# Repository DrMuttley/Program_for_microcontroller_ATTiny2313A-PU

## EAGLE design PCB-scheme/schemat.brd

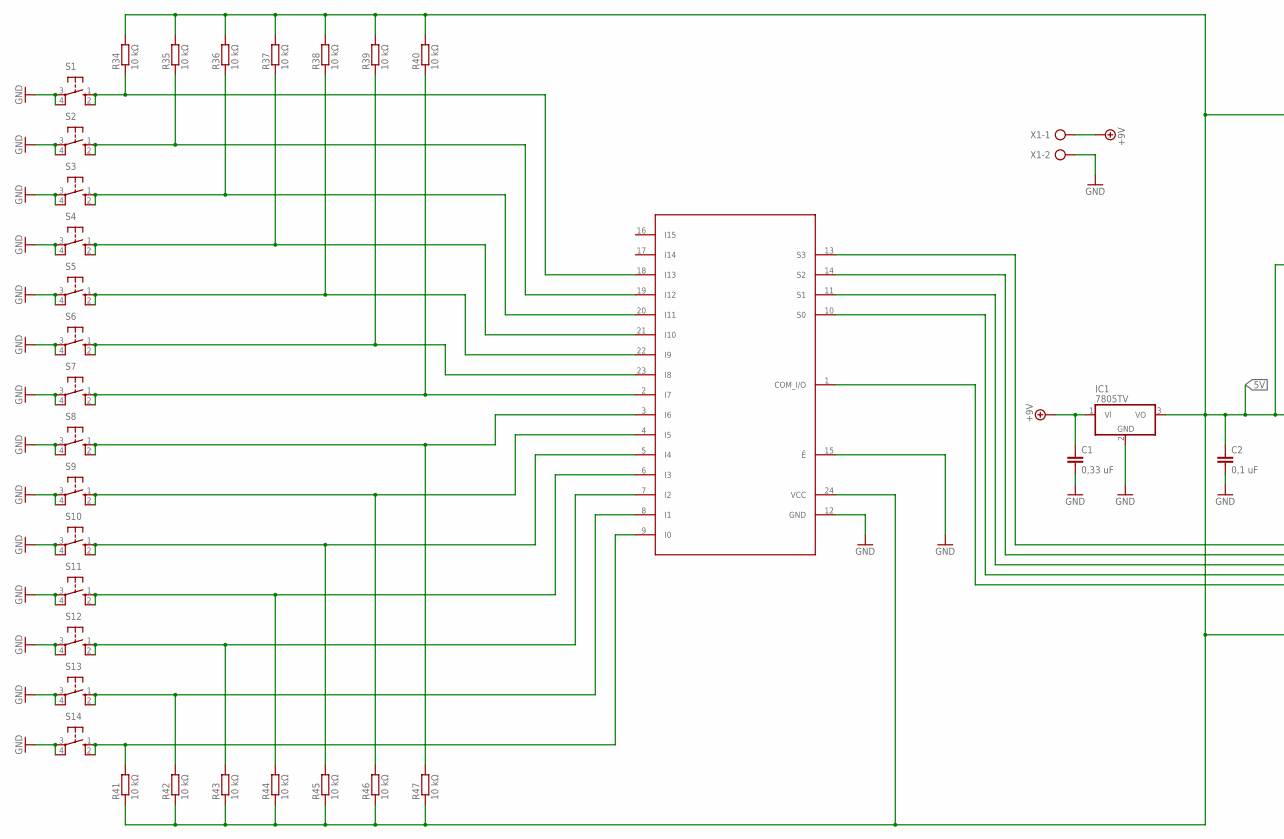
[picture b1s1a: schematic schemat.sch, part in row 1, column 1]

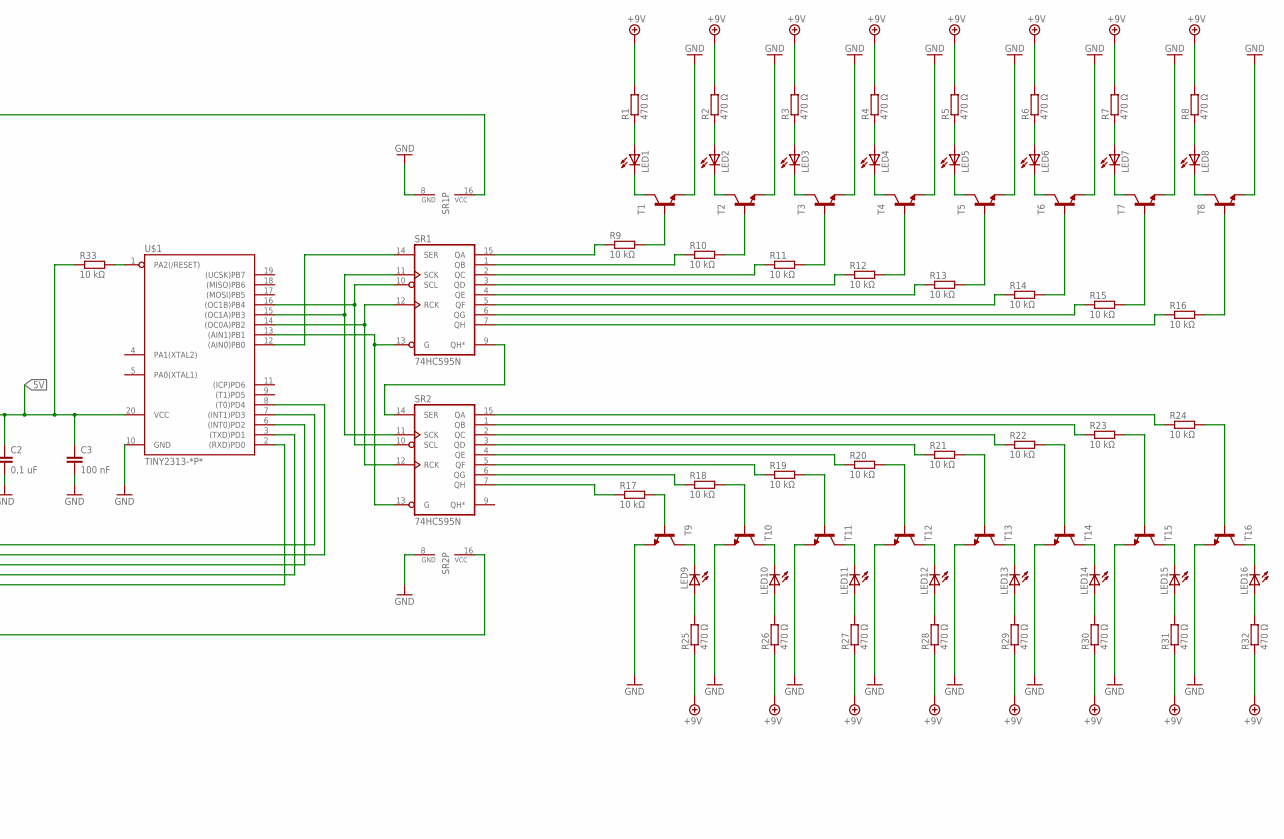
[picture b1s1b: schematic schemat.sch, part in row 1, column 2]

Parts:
C1: 0,33 uF; C025-024X044
C2: 0,1 uF; C025-024X044
C3: 100 nF; C025-024X044
IC1: 7805TV; TO220V
LED1, LED2, LED3, LED4, LED5, LED6, LED7, LED8, LED9, LED10, LED11, LED12, LED13, LED14, LED15, LED16: LED5MM
R1, R2, R3, R4, R5, R6, R7, R8, R25, R26, R27, R28, R29, R30, R31, R32: 470 Ω; 0207/10
R9, R10, R11, R12, R13, R14, R15, R16, R17, R18, R19, R20, R21, R22, R23, R24, R33, R34, R35, R36, R37, R38, R39, R40, R41, R42, R43, R44, R45, R46, R47: 10 kΩ; 0207/10
S1, S2, S3, S4, S5, S6, S7, S8, S9, S10, S11, S12, S13, S14: 40-XX; B3F-40XX
SR1, SR2: 74HC595N; DIL16
T1, T2, T3, T4, T5, T6, T7, T8, T9, T10, T11, T12, T13, T14, T15, T16: -NPN-TO92; TO92
U$1: TINY2313-*P*; DIL20
U$2: CD74HC4067; DIL24-6
X1: AK500/2

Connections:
5V: C2.1, C3.1, IC1.3 (VO), R33.1, R34.2, R35.2, R36.2, R37.2, R38.2, R39.2, R40.2, R41.1, R42.1, R43.1, R44.1, R45.1, R46.1, R47.1, SR1.16 (VCC), SR2.16 (VCC), U$1.20 (VCC), U$2.24 (VCC)
+9V: C1.1, IC1.1 (VI), R1.2, R2.2, R3.2, R4.2, R5.2, R6.2, R7.2, R8.2, R25.1, R26.1, R27.1, R28.1, R29.1, R30.1, R31.1, R32.1, X1.1
GND: C1.2, C2.2, C3.2, IC1.2 (GND), S1.3, S1.4 (P1), S2.3, S2.4 (P1), S3.3, S3.4 (P1), S4.3, S4.4 (P1), S5.3, S5.4 (P1), S6.3, S6.4 (P1), S7.3, S7.4 (P1), S8.3, S8.4 (P1), S9.3, S9.4 (P1), S10.3, S10.4 (P1), S11.3, S11.4 (P1), S12.3, S12.4 (P1), S13.3, S13.4 (P1), S14.3, S14.4 (P1), SR1.8 (GND), SR2.8 (GND), T1.1 (E), T2.1 (E), T3.1 (E), T4.1 (E), T5.1 (E), T6.1 (E), T7.1 (E), T8.1 (E), T9.1 (E), T10.1 (E), T11.1 (E), T12.1 (E), T13.1 (E), T14.1 (E), T15.1 (E), T16.1 (E), U$1.10 (GND), U$2.12 (GND), U$2.15 (Ē), X1.2
unnamed: SR1.9 (QH*), SR2.14 (SER)
unnamed: SR1.12 (RCK), SR2.12 (RCK), U$1.14 ((OC0A)PB2)
unnamed: R33.2, U$1.1 (PA2(/RESET))
unnamed: R42.2, S13.1 (S), S13.2 (S1), U$2.8 (I1)
unnamed: R43.2, S12.1 (S), S12.2 (S1), U$2.7 (I2)
unnamed: SR1.10 (SCL), SR2.10 (SCL), U$1.16 ((OC1B)PB4)
unnamed: LED1.A, R1.1
unnamed: R9.2, T1.2 (B)
unnamed: R10.1, SR1.1 (QB)
unnamed: R10.2, T2.2 (B)
unnamed: R9.1, SR1.15 (QA)
unnamed: R11.2, T3.2 (B)
unnamed: R11.1, SR1.2 (QC)
unnamed: R12.2, T4.2 (B)
unnamed: R12.1, SR1.3 (QD)
unnamed: R13.2, T5.2 (B)
unnamed: R13.1, SR1.4 (QE)
unnamed: R14.1, SR1.5 (QF)
unnamed: R14.2, T6.2 (B)
unnamed: R15.2, T7.2 (B)
unnamed: R16.2, T8.2 (B)
unnamed: R15.1, SR1.6 (QG)
unnamed: R16.1, SR1.7 (QH)
unnamed: LED1.K (C), T1.3 (C)
unnamed: LED2.K (C), T2.3 (C)
unnamed: LED3.K (C), T3.3 (C)
unnamed: LED4.K (C), T4.3 (C)
unnamed: LED5.K (C), T5.3 (C)
unnamed: LED6.K (C), T6.3 (C)
unnamed: LED7.K (C), T7.3 (C)
unnamed: LED8.K (C), T8.3 (C)
unnamed: LED2.A, R2.1
unnamed: LED3.A, R3.1
unnamed: LED4.A, R4.1
unnamed: LED5.A, R5.1
unnamed: LED6.A, R6.1
unnamed: LED7.A, R7.1
unnamed: LED8.A, R8.1
unnamed: LED9.A, R25.2
unnamed: R17.2, T9.2 (B)
unnamed: LED9.K (C), T9.3 (C)
unnamed: LED10.K (C), T10.3 (C)
unnamed: LED11.K (C), T11.3 (C)
unnamed: LED12.K (C), T12.3 (C)
unnamed: LED13.K (C), T13.3 (C)
unnamed: LED14.K (C), T14.3 (C)
unnamed: LED15.K (C), T15.3 (C)
unnamed: LED16.K (C), T16.3 (C)
unnamed: R17.1, SR2.7 (QH)
unnamed: R18.1, SR2.6 (QG)
unnamed: R18.2, T10.2 (B)
unnamed: R19.1, SR2.5 (QF)
unnamed: R19.2, T11.2 (B)
unnamed: R20.2, T12.2 (B)
unnamed: R20.1, SR2.4 (QE)
unnamed: R21.2, T13.2 (B)
unnamed: R21.1, SR2.3 (QD)
unnamed: R22.2, T14.2 (B)
unnamed: R22.1, SR2.2 (QC)
unnamed: R23.2, T15.2 (B)
unnamed: R23.1, SR2.1 (QB)
unnamed: R24.2, T16.2 (B)
unnamed: R24.1, SR2.15 (QA)
unnamed: LED10.A, R26.2
unnamed: LED11.A, R27.2
unnamed: LED12.A, R28.2
unnamed: LED13.A, R29.2
unnamed: LED14.A, R30.2
unnamed: LED15.A, R31.2
unnamed: LED16.A, R32.2
unnamed: R41.2, S14.1 (S), S14.2 (S1), U$2.9 (I0)
unnamed: SR1.13 (G), SR2.13 (G), U$1.13 ((AIN1)PB1)
unnamed: R44.2, S11.1 (S), S11.2 (S1), U$2.6 (I3)
unnamed: SR1.11 (SCK), SR2.11 (SCK), U$1.15 ((OC1A)PB3)
unnamed: R45.2, S10.1 (S), S10.2 (S1), U$2.5 (I4)
unnamed: R46.2, S9.1 (S), S9.2 (S1), U$2.4 (I5)
unnamed: R47.2, S8.1 (S), S8.2 (S1), U$2.3 (I6)
unnamed: R34.1, S1.1 (S), S1.2 (S1), U$2.18 (I13)
unnamed: R35.1, S2.1 (S), S2.2 (S1), U$2.19 (I12)
unnamed: R36.1, S3.1 (S), S3.2 (S1), U$2.20 (I11)
unnamed: R37.1, S4.1 (S), S4.2 (S1), U$2.21 (I10)
unnamed: R38.1, S5.1 (S), S5.2 (S1), U$2.22 (I9)
unnamed: R39.1, S6.1 (S), S6.2 (S1), U$2.23 (I8)
unnamed: R40.1, S7.1 (S), S7.2 (S1), U$2.2 (I7)
unnamed: U$1.2 ((RXD)PD0), U$2.1 (COM_I/O)
unnamed: U$1.3 ((TXD)PD1), U$2.10 (S0)
unnamed: U$1.6 ((INT0)PD2), U$2.11 (S1)
unnamed: U$1.8 ((T0)PD4), U$2.14 (S2)
unnamed: U$1.7 ((INT1)PD3), U$2.13 (S3)
unnamed: SR1.14 (SER), U$1.12 ((AIN0)PB0)

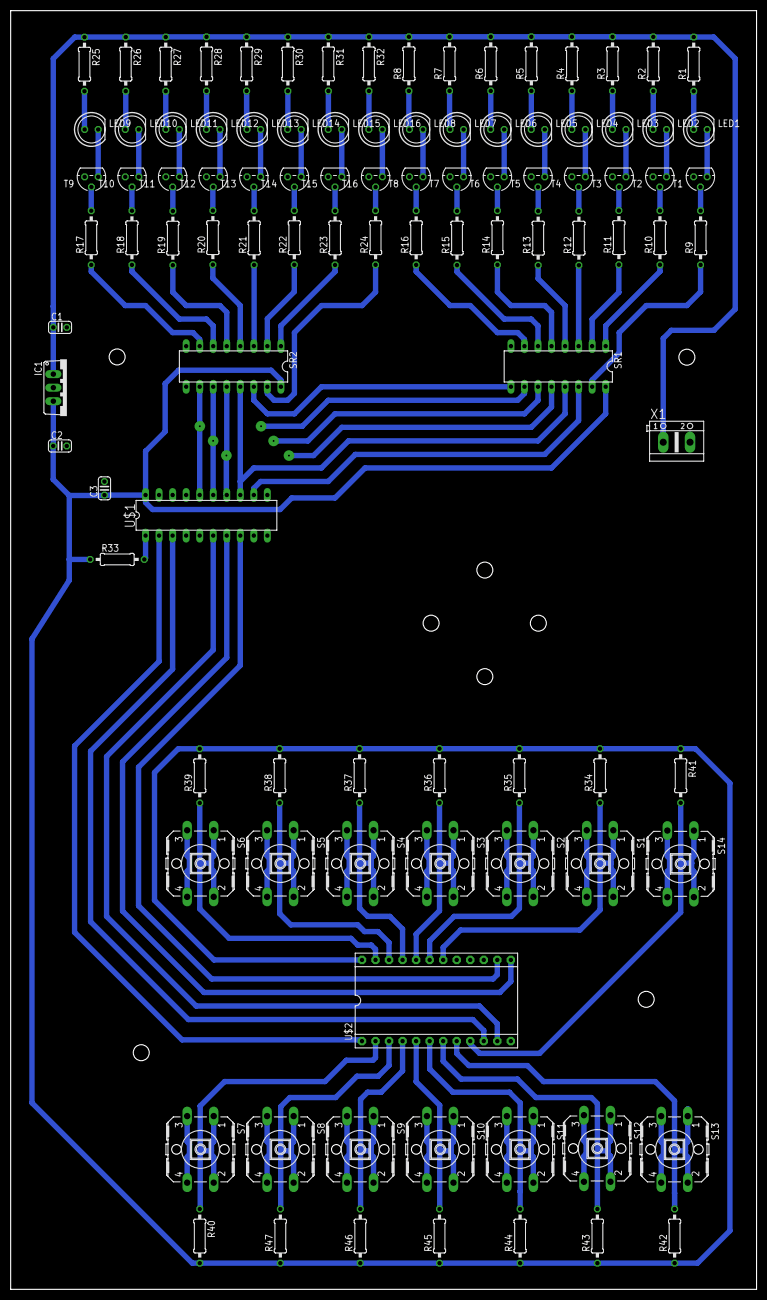
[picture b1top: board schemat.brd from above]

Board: 2 copper layers, 140.0 x 240.0 mm, 102 parts (0 on the bottom side), 93 nets.

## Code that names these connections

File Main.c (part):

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#include <string.h>

/*obsługa rejestrów*/
#define SER PB0
#define G PB1  //rck
#define RCK PB2//SCK
#define SCK PB3 //SCLR
#define SCLR PB4

/*obsługa multiplekser*/
#define S0 PD1  //PD0
#define S1 PD2  //PD1
#define S2 PD4  //PD2
#define S3 PD3  //PD3
#define BUTTON (1<<PD0)  //PD4

void setS0S3_AsOut();
void setButtonAsIn();
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
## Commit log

2018-10-04 Version 1.0
    Final application for version 1.0
